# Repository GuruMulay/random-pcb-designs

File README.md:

View this project on [CADLAB.io](https://cadlab.io/project/1371). 

This repo contains a bunch PCB that I designed during my undergrad as a part of my college's robotics team. Read more about these projects [here](https://gurumulay.github.io/electronics/) and [here](https://gurumulay.github.io/robotics/).

List of projects:
* Atmega32uc3 Prototype PCB
* FTDI chip based Programmer PCB for AVR Micro-controllers
* Comparator Board for a Line-sensor
* Pneumatic Piston Driver PCB
* Transmitter Board
* ULN IC Board
* PTN Voltage Regulator PCB

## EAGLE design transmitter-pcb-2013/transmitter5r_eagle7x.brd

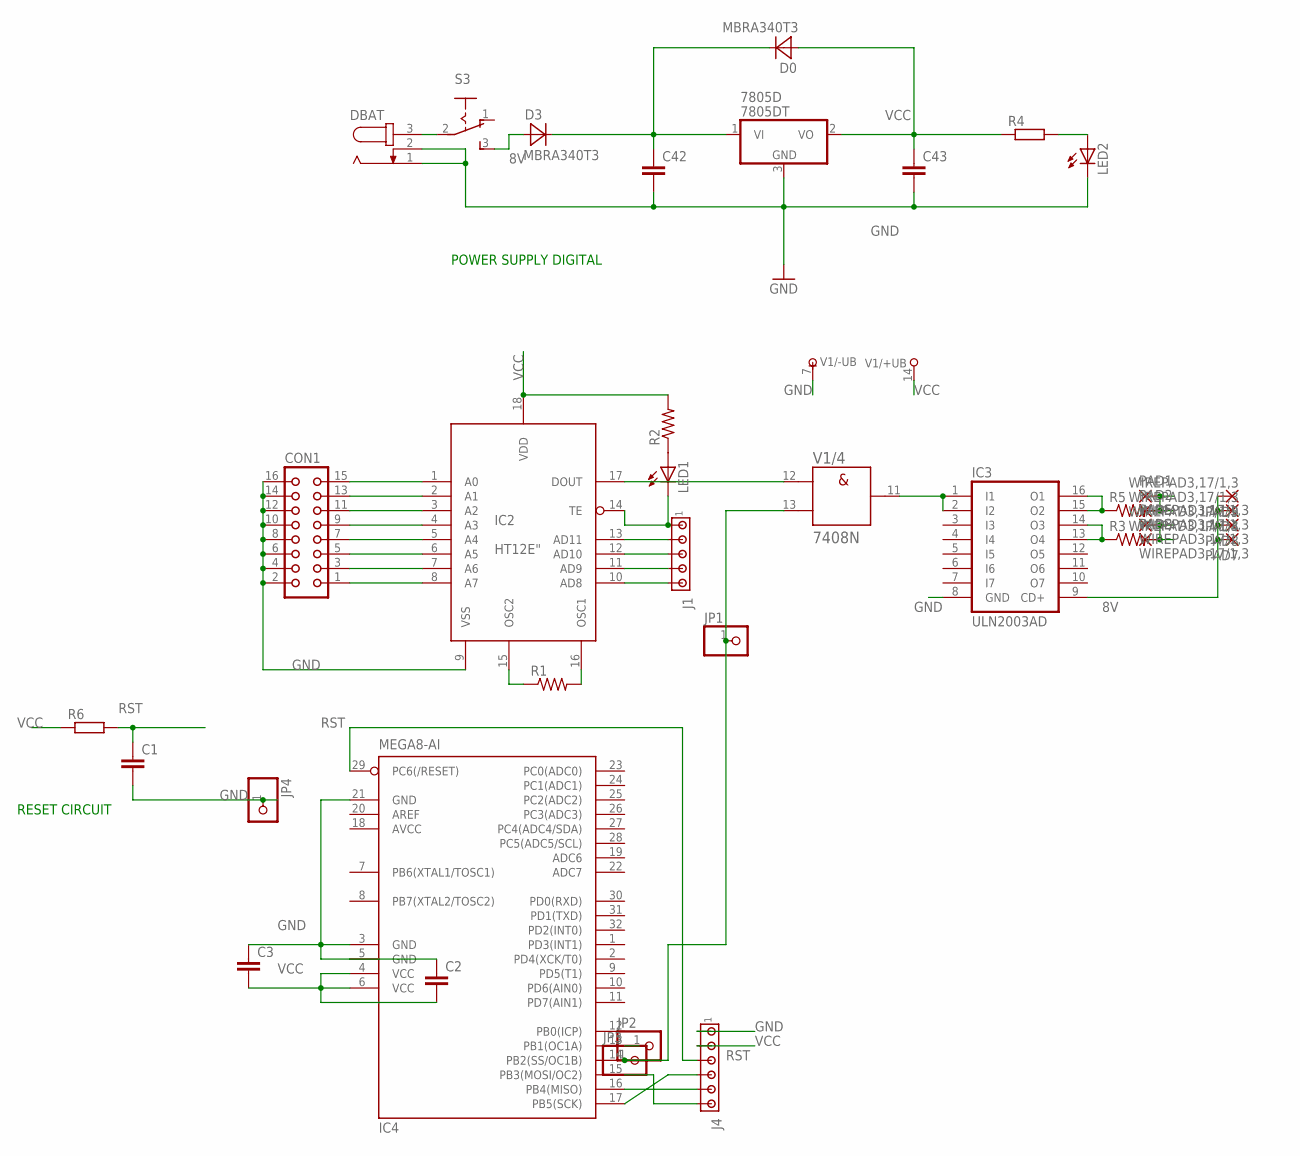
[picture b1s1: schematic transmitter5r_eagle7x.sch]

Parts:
7805D: 7805DT; TO252
C1, C2, C3, C42, C43: C-EUC0603; C0603
CON1: CON16
D0, D3: MBRA340T3; SMA
DBAT: JACK-PLUG0; SPC4077
IC2: HT12E"; 18-DIP-A
IC3: ULN2003AD; SO16
IC4: MEGA8-AI; TQFP32-08
J1: MTA05-100; 10X05MTA
J4: MTA06-100; 10X06MTA
JP1, JP2, JP3, JP4: PINHD-1X1; 1X01
LED1, LED2: LED3MM
PAD1, PAD2, PAD3, PAD4, PAD5, PAD7, PAD8, PAD9: WIREPAD3,17/1,3; 3,17/1,3
R1: R-US_VMTA55; VMTA55
R2: R-US_M1206; M1206
R3, R5: R-US_0309/12; 0309/12
R4, R6: R-EU_R0603; R0603
S3: 255SB
V1: 7408N; DIL14

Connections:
8V: D3.A, IC3.9 (CD+), PAD4.1, PAD7.1, PAD8.1, PAD9.1, S3.3 (S)
AVCC: IC4.18 (AVCC)
GND: 7805D.3 (GND), C1.2, C2.1, C3.1, C42.2, C43.2, CON1.2, CON1.4, CON1.6, CON1.8, CON1.10, CON1.12, CON1.14, CON1.16, DBAT.1, DBAT.2, IC2.9 (VSS), IC3.8 (GND), IC4.3 (GND), IC4.5 (GND), IC4.21 (GND), J4.6 (1), JP4.1, LED2.K (C), V1.7 (-UB)
unnamed: CON1.15, IC2.1 (A0)
unnamed: CON1.13, IC2.2 (A1)
unnamed: CON1.11, IC2.3 (A2)
unnamed: CON1.9, IC2.4 (A3)
unnamed: CON1.7, IC2.5 (A4)
unnamed: DBAT.3, S3.2
unnamed: IC3.15 (O2), IC3.16 (O1), R5.1
unnamed: LED2.A, R4.2
unnamed: CON1.5, IC2.6 (A5)
unnamed: CON1.3, IC2.7 (A6)
unnamed: CON1.1, IC2.8 (A7)
unnamed: IC2.13 (AD11), J1.2
unnamed: IC2.12 (AD10), J1.3
unnamed: IC2.11 (AD9), J1.4
unnamed: IC2.10 (AD8), J1.5
unnamed: IC2.16 (OSC1), R1.2
unnamed: IC2.15 (OSC2), R1.1
unnamed: IC4.14 (PB2(SS/OC1B)), JP1.1, JP3.1, V1.13 (B)
unnamed: IC3.13 (O4), IC3.14 (O3), R3.1
unnamed: PAD3.1, PAD5.1, R3.2
unnamed: IC2.17 (DOUT), V1.12 (A)
unnamed: LED1.A, R2.1
unnamed: IC3.1 (I1), IC3.2 (I2), V1.11 (Y)
unnamed: IC4.15 (PB3(MOSI/OC2)), J4.1 (6)
unnamed: PAD1.1, PAD2.1, R5.2
unnamed: IC4.16 (PB4(MISO)), J4.2 (5)
unnamed: IC4.17 (PB5(SCK)), J4.3 (4)
unnamed: IC4.13 (PB1(OC1A)), JP2.1
RST: C1.1, IC4.29 (PC6(/RESET)), J4.4 (3), R6.2
TE: IC2.14 (TE), J1.1, LED1.K (C)
VCC: 7805D.2 (VO), C2.2, C3.2, C43.1, D0.A, IC2.18 (VDD), IC4.4 (VCC), IC4.6 (VCC), J4.5 (2), R2.2, R4.1, R6.1, V1.14 (+UB)
VI(5D): 7805D.1 (VI), C42.1, D0.C, D3.C

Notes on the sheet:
POWER SUPPLY DIGITAL
RESET CIRCUIT

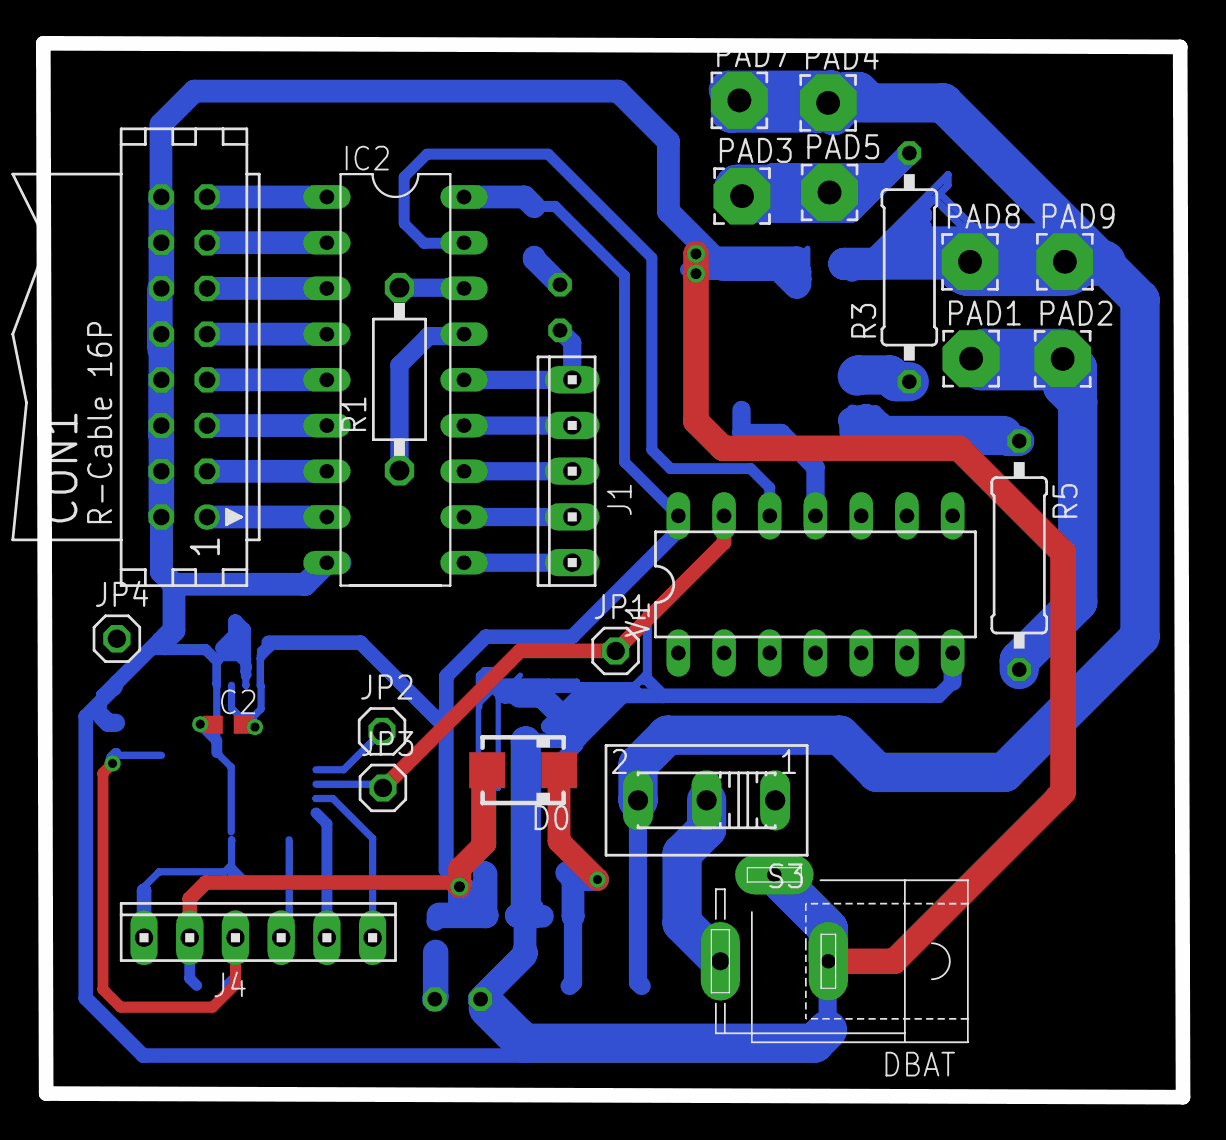
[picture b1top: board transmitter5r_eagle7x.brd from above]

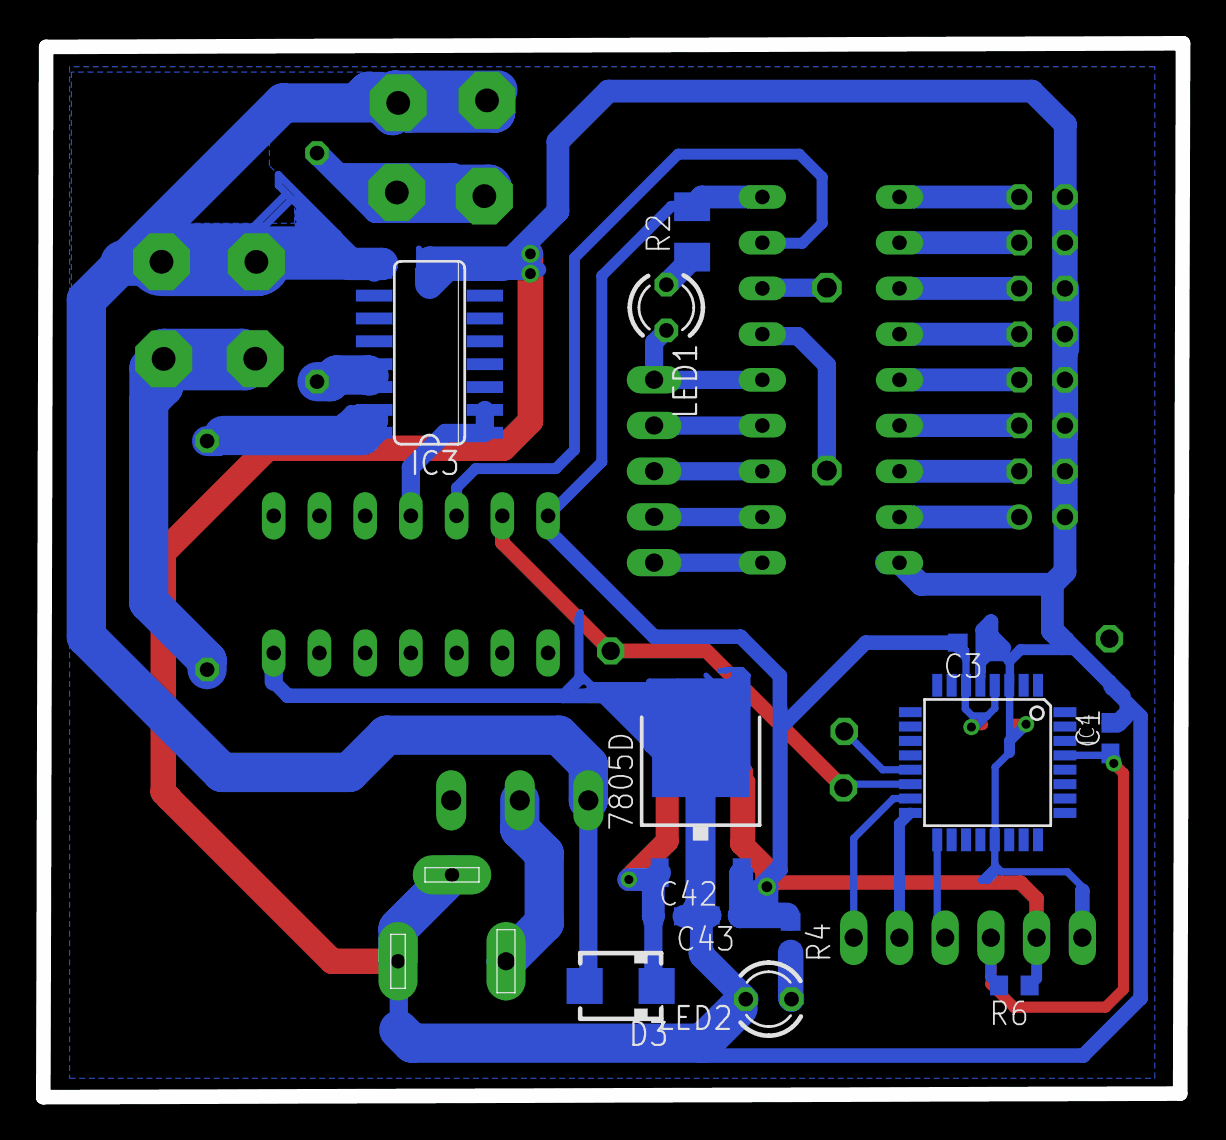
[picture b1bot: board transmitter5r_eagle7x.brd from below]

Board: 2 copper layers, 63.3 x 58.5 mm, 37 parts (13 on the bottom side), 34 nets.

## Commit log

2018-10-13 Add readme
2018-10-13 Add content list to readme
2018-10-14 Add project: atmega32 prototype pcb - pdfs and images of board and schematics
2018-10-14 Add schematic and board files, latest version is v7
2018-10-14 Add FTDI proj: pdfs and images
2018-10-14 Add schematic and board files, eagle7x files as well
2018-10-14 Fixed readme typo
2018-10-14 Comparator PCB add pdfs and images
2018-10-14 Add comparator board schematics and board files
2018-10-14 Add proj: piston driver pcb: pdfs and images of schematics and boards
2018-10-14 piston ptn pcb: add gerber files
2018-10-14 Add various versions of piston ptn boards
2018-10-14 Add uln-dual pcb project: pdfs and images of schematics and boards
2018-10-14 dual uln pcb: add gerber files
2018-10-14 dual uln pcb: add scheamtic and board files
2018-10-14 TODO proj: two atmega32 on a board
2018-10-14 Add transmitter board: pdfs and images of schematics and boards
2018-10-14 transmitter pcb: add scheamtic and board files
2018-10-14 Backlink to CADLAB.io has been added.
2018-10-31 add schematic image
2018-11-02 rearranged images
